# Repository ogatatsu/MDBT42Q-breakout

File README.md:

# MDBT42Q-breakout

Raytac社製nRF52832モジュールMDBT42Qのブレークアウト基板です。

RedBearLabのBLE Nanoの書き込み機(Daplink)を直接挿して書き込みできるようにしました。

コンデンサ、インダクタはすべて1608サイズ、水晶振動子はFC-135です。
コンデンサC2,C3の容量は水晶振動子の負荷容量に合わせて選定してください。
コンデンサはその辺の店に売ってると思いますがインダクタはなかなか厳しいと思いますので私が使用したものの入手先を貼っておきます。

- 15nH
  - https://www.digikey.jp/product-detail/ja/taiyo-yuden/HK160815NJ-T/587-1547-1-ND/1008162
  - https://www.marutsu.co.jp/GoodsDetail.jsp?q=HK160815NJ-T&salesGoodsCode=15560264
- 10µH
  - https://www.digikey.jp/product-detail/ja/taiyo-yuden/LBMF1608T100K/587-1714-1-ND/1008036
  - https://www.marutsu.co.jp/GoodsDetail.jsp?q=LBMF1608T100K&salesGoodsCode=15560538

## License

https://creativecommons.org/licenses/by/4.0/

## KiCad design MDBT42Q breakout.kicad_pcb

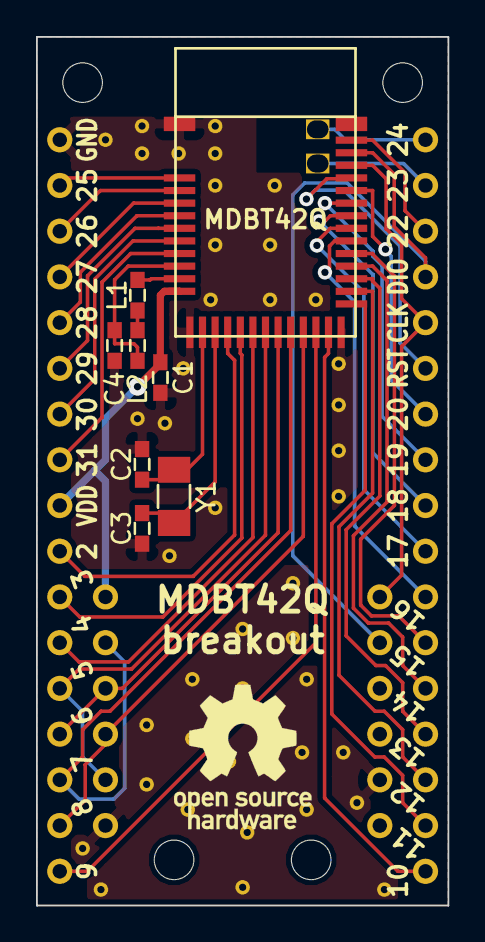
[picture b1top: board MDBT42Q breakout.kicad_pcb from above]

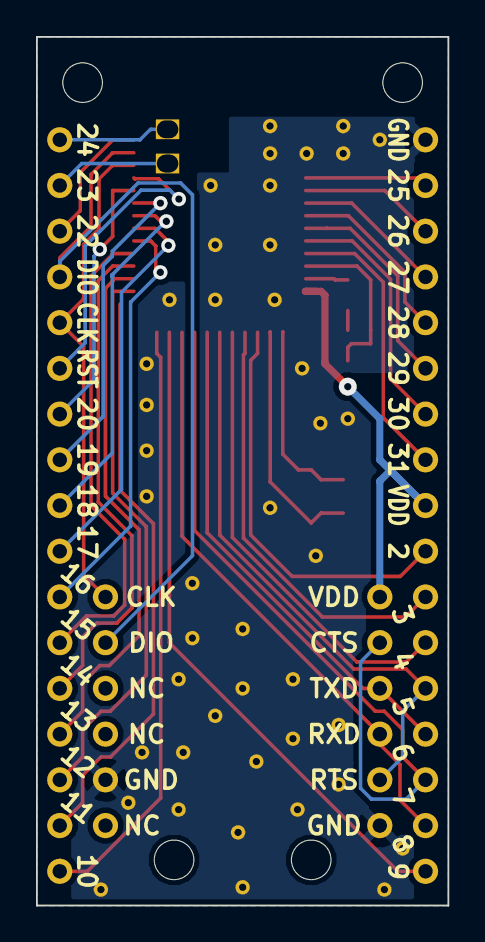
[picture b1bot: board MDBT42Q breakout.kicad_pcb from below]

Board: 2 copper layers, 22.9 x 48.3 mm, 54 parts (12 on the bottom side), 39 nets.

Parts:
C1: 10μF; 1608
C2, C3: //pF; 1608
C4: 1μF; 1608
J1: 25; Wirepad
J2: 26; Wirepad
J3: 27; Wirepad
J4: 28; Wirepad
J5: 29; Wirepad
J6: 30; Wirepad
J7: 31; Wirepad
J8, J41: VDD; Wirepad
J9: 2; Wirepad
J10: 3; Wirepad
J11: 4; Wirepad
J12: 5; Wirepad
J13: 6; Wirepad
J14: 7; Wirepad
J15: 8; Wirepad
J16: 9; Wirepad
J17: 10; Wirepad
J18: 24; Wirepad
J19: 23; Wirepad
J20: 22; Wirepad
J21, J36: DIO; Wirepad
J22, J35: CLK; Wirepad
J23: RST; Wirepad
J24: 20; Wirepad
J25: 19; Wirepad
J26: 18; Wirepad
J27: 17; Wirepad
J28: 16; Wirepad
J29: 15; Wirepad
J30: 14; Wirepad
J31: 13; Wirepad
J32: 12; Wirepad
J33: 11; Wirepad
J34, J39, J46: GND; Wirepad
J37, J38, J40: NC; Wirepad
J42: CTS; Wirepad
J43: TXD; Wirepad
J44: RXD; Wirepad
J45: RTS; Wirepad
L1: 10μH; 1608
L2: 15nH; 1608
U1: MDBT42Q
Y1: 32.768kHz; FC-135

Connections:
2: J9.1, U1.15
3: J10.1, U1.16
4: J11.1, U1.17
5: J12.1, J45.1, U1.18
6: J13.1, J43.1, U1.19
7: J14.1, J42.1, U1.20
8: J15.1, J44.1, U1.21
9: J16.1, U1.22
10: J17.1, U1.23
11: J33.1, U1.25
12: J32.1, U1.26
13: J31.1, U1.27
14: J30.1, U1.28
15: J29.1, U1.29
16: J28.1, U1.30
17: J27.1, U1.31
18: J26.1, U1.32
19: J25.1, U1.33
20: J24.1, U1.34
22: J20.1, U1.38
23: J19.1, U1.41
24: J18.1, U1.40
25: J1.1, U1.2
26: J2.1, U1.3
27: J3.1, U1.4
28: J4.1, U1.5
29: J5.1, U1.6
30: J6.1, U1.7
31: J7.1, U1.8
CLK: J22.1, J35.1, U1.36
DIO: J21.1, J36.1, U1.37
GND: C1.2, C2.2, C3.2, C4.1, J34.1, J39.1, J46.1, U1.1, U1.12, U1.24
unnamed: C2.1, U1.13, Y1.1
unnamed: C3.1, U1.14, Y1.2
unnamed: C4.2, L2.2, U1.9
unnamed: L1.1, U1.10
unnamed: L1.2, L2.1
RST: J23.1, U1.35
VDD: C1.1, J8.1, J41.1, U1.11

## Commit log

2017-09-02 add schematic
2017-09-02 change c2 c3 capacity
2017-09-02 add images
2017-09-02 change schematic
2017-11-05 libファイルが入っていなかったので追加
